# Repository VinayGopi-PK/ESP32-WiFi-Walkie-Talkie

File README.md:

# ESP32 Wi-Fi Walkie-Talkie

An **ESP32-based real-time Wi-Fi Walkie-Talkie** designed for voice communication using **UDP audio streaming**. The system uses an **INMP441 I2S digital microphone**, **MAX98357A I2S audio amplifier**, and a **Push-to-Talk (PTT)** control.

The hardware was designed in **KiCad**, including the schematic, PCB layout, and 3D visualization. The repository also contains the ESP32 Arduino source code and Gerber files for PCB manufacturing.

---

## Project Overview

This project is a wireless voice communication system based on two ESP32 boards communicating over Wi-Fi.

The voice signal is captured by the **INMP441 digital microphone** through the I2S interface. The ESP32 processes and transmits the audio data using **UDP over Wi-Fi**. At the receiving side, the audio is sent through I2S to the **MAX98357A audio amplifier**, which drives the speaker.

A **Push-to-Talk (PTT)** button is used to control voice transmission.

### Audio Communication Path

```text
Voice
  ↓
INMP441 I2S Microphone
  ↓
ESP32
  ↓
UDP Audio Streaming over Wi-Fi
  ↓
ESP32
  ↓
MAX98357A I2S Audio Amplifier
  ↓
Speaker
```

---

## Main Features

* ESP32-based wireless communication
* Real-time UDP audio streaming
* Wi-Fi-based voice communication
* I2S digital audio interface
* INMP441 I2S digital microphone
* MAX98357A I2S audio amplifier
* Push-to-Talk (PTT) control
* Custom PCB designed using KiCad
* Complete schematic design
* PCB layout design
* Front and back PCB layout
* 3D PCB visualization
* Gerber files for PCB manufacturing

---

## Hardware

| Component           | Function                                     |
| ------------------- | -------------------------------------------- |
| ESP32               | Main microcontroller and Wi-Fi communication |
| INMP441             | I2S digital microphone                       |
| MAX98357A           | I2S audio amplifier                          |
| Push-to-Talk Button | Controls voice transmission                  |
| Speaker             | Audio output                                 |
| Custom PCB          | Integrates the system hardware               |

---

## Software

The ESP32 firmware was developed using **Arduino IDE**.

The repository contains the final Arduino source code used for the ESP32 Walkie-Talkie system.

### Communication

* Wireless technology: **Wi-Fi**
* Communication protocol: **UDP**
* Audio interface: **I2S**

---

## PCB Design

The custom PCB was designed using **KiCad**.

The PCB design includes:

* Complete schematic
* Component placement
* PCB routing
* Front copper layout
* Back copper layout
* Power and signal routing
* 3D PCB visualization
* Gerber manufacturing files

---

## PCB Design Preview

### Schematic

### PCB Front Layout

### PCB Back Layout

### 3D View

---

## Repository Contents

### KiCad Design Files

The `ESP32_Walkie-Talkie Files` folder contains the KiCad project files, including:

* KiCad project file
* KiCad schematic
* KiCad PCB layout
* Component/project data files

### Arduino Source Code

The `Final_Codes` folder contains the final ESP32 Arduino source code for the Walkie-Talkie system.

### Gerber Files

The `Gerber Files_4_ESP32 Walkie-Talkie` folder contains the generated Gerber files required for PCB manufacturing.

### Project Images

The `Images_4_ESP32-Walkie-Talkie` folder contains:

* Schematic image
* PCB front layout
* PCB back layout
* PCB 3D view

---

## Design Tools

* **KiCad** — Schematic and PCB design
* **Arduino IDE** — ESP32 firmware development

---

## Technical Highlights

**Microcontroller:** ESP32
**Wireless Communication:** Wi-Fi
**Communication Protocol:** UDP
**Audio Interface:** I2S
**Digital Microphone:** INMP441
**Audio Amplifier:** MAX98357A
**Control:** Push-to-Talk (PTT)

---

## Project Objective

The objective of this project was to develop an **ESP32-based wireless voice communication system** while combining embedded programming, Wi-Fi networking, real-time UDP audio streaming, digital I2S audio, schematic design, PCB layout, and PCB manufacturing file generation.

---

## Project Type

**ESP32 Embedded System | Wi-Fi Communication | Digital Audio | PCB Design**

**Design Software:** KiCad
**Programming Environment:** Arduino IDE

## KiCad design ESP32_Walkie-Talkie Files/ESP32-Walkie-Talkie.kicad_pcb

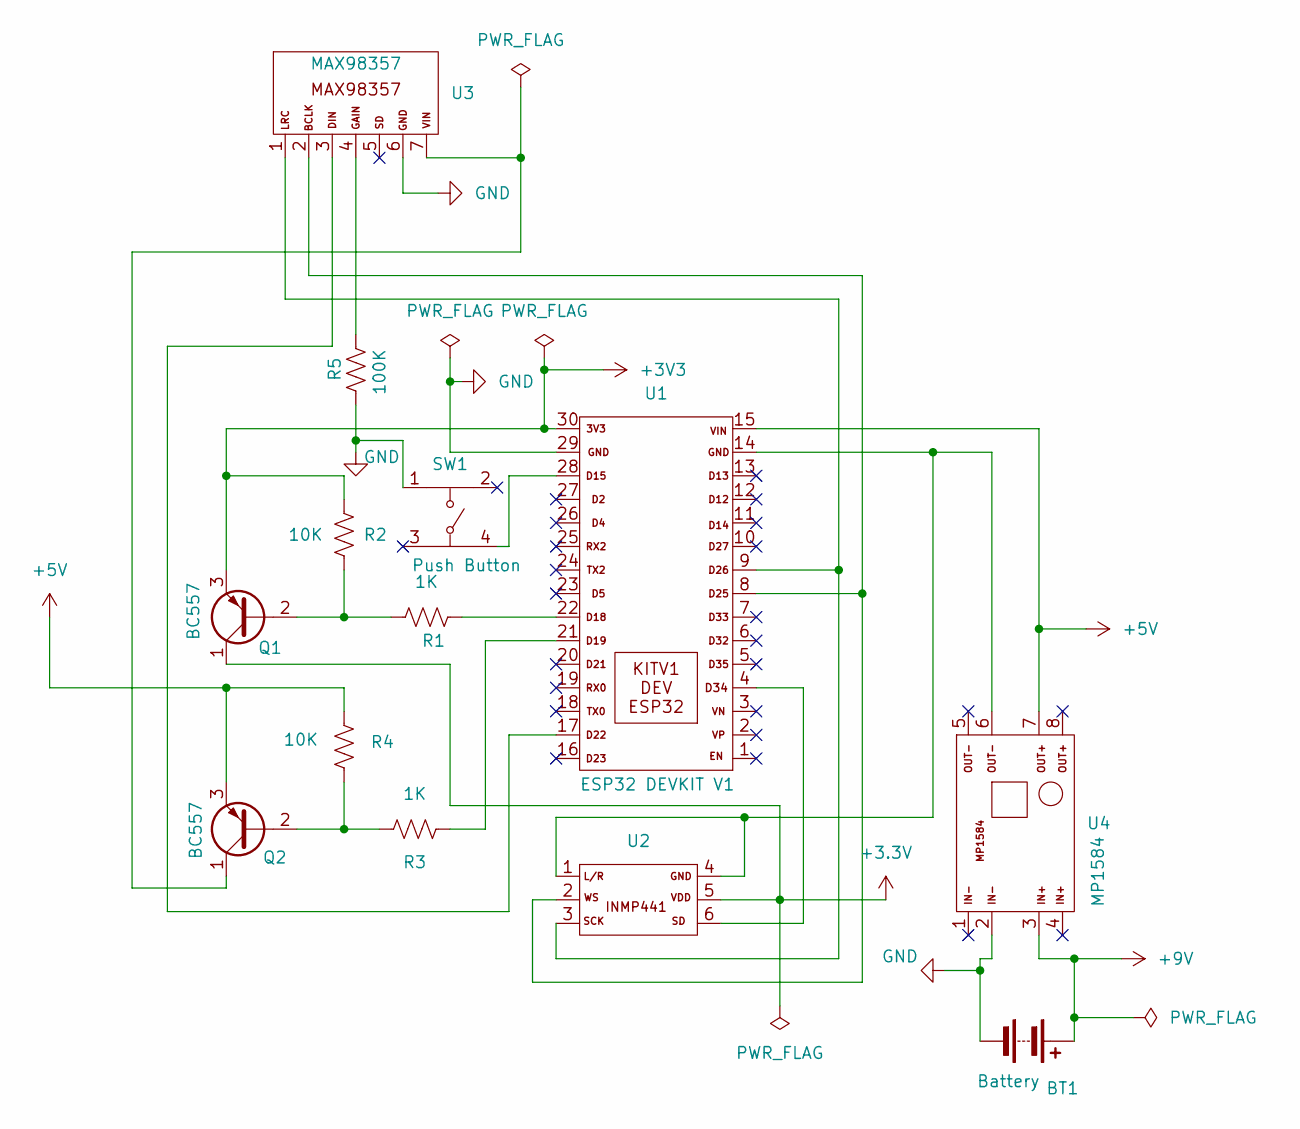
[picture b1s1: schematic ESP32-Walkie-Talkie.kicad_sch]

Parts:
BT1: Battery; BatteryHolder_Eagle_12BH611-GR
Q1, Q2: BC557; TO-92_Inline
R1, R3: 1K; R_Axial_DIN0309_L9.0mm_D3.2mm_P12.70mm_Horizontal
R2, R4: 10K; R_Axial_DIN0309_L9.0mm_D3.2mm_P12.70mm_Horizontal
R5: 100K; R_Axial_DIN0309_L9.0mm_D3.2mm_P12.70mm_Horizontal
SW1: Push Button; Footprint_Button_Tactile_6x6mm
U1: ESP32 DEVKIT V1; ESP32_DevKit_30Pin_Socket
U2: INMP441
U3: MAX98357
U4: MP1584

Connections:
+3.3V: Q1.1 (C), U2.5 (VDD)
+3V3: Q1.3 (E), R2.1, U1.30 (3V3)
+5V: Q2.3 (E), R4.1, U1.15 (VIN), U4.7 (OUT+)
+9V: BT1.1 (+), U4.3 (IN+)
GND: BT1.2 (-), R5.2, SW1.1, U1.29 (GND), U3.6 (GND), U4.2 (IN-)
unnamed: Q1.2 (B), R1.1, R2.2
unnamed: Q2.2 (B), R3.1, R4.2
unnamed: Q2.1 (C), U3.7 (VIN)
unnamed: SW1.4, U1.28 (D15)
unnamed: R1.2, U1.22 (D18)
unnamed: R3.2, U1.21 (D19)
unnamed: U1.17 (D22), U3.3 (DIN)
unnamed: U1.8 (D25), U2.2 (WS), U3.2 (BCLK)
unnamed: U1.9 (D26), U2.3 (SCK), U3.1 (LRC)
unnamed: U1.4 (D34), U2.6 (SD)
unnamed: U1.14 (GND), U2.1 (L/R), U2.4 (GND), U4.6 (OUT-)
unnamed: R5.1, U3.4 (GAIN)

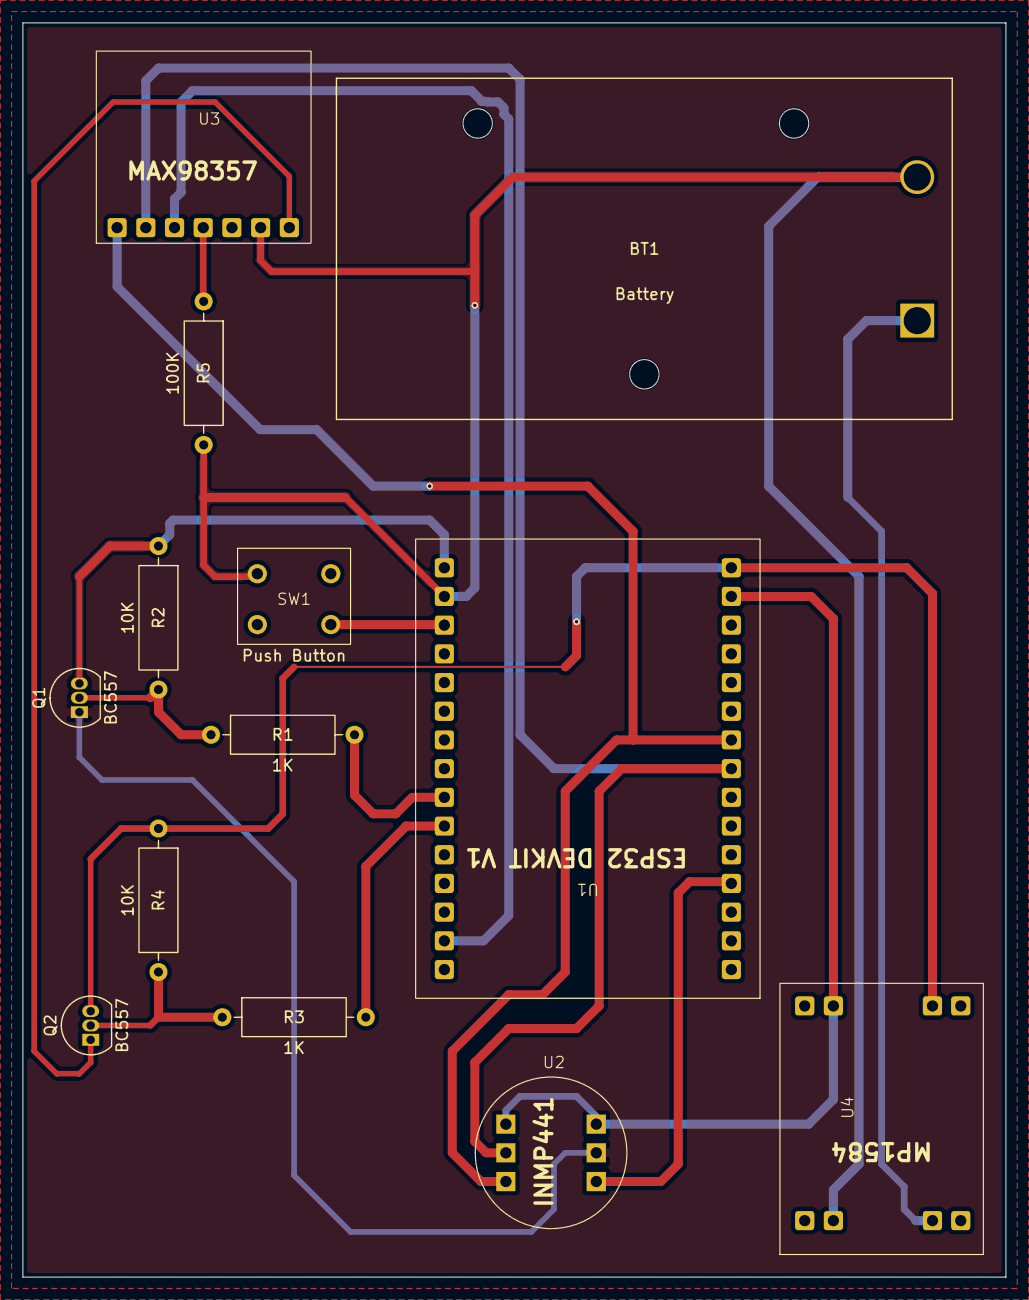
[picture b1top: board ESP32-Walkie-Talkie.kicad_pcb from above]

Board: 2 copper layers, 87.0 x 111.0 mm, 13 parts (0 on the bottom side), 17 nets.
